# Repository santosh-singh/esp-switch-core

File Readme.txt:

Each device will have its own unique id ... chipid ... ESP.getChipId()
setup()
  When the device is powered on it will check for the ssid password in EEPROM ... and try to connect
  If connected it will resume client mode ... else ... AP mode
    Client mode:
      get deviceid from EEPROM address 100 - 150
      if device does not exist then this device is not registered online
      Check if not device is registered online? /api/1.0/register?deviceid=chipid = returns new deviceid  
      store the deviceid in EEPROM address 100 - 150
      now loop ...
    AP Mode:
      WiFi.mode(WIFI_AP_STA);
      WiFi.softAP( ssid.c_str() );
      Launch Web Server & DNS Server
      display page with SSID list and ask to select one with password.
      attempt to connect as WIFI_STA
      if successful, ESP.restart() else WIFI_display page again ...

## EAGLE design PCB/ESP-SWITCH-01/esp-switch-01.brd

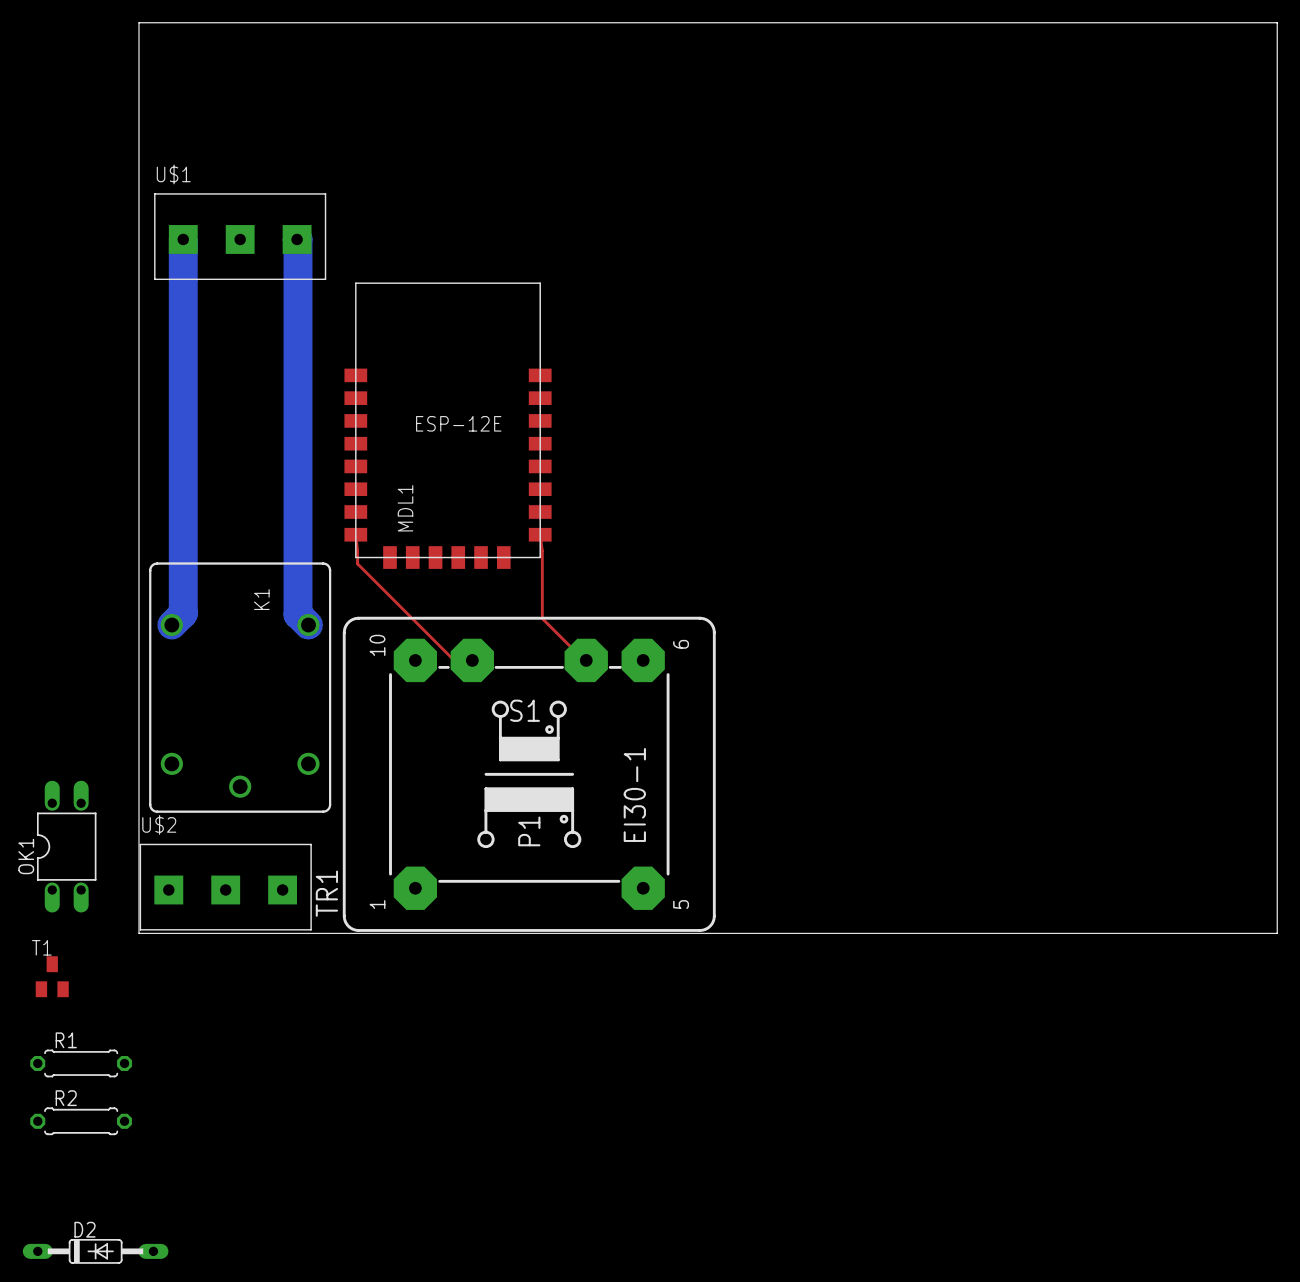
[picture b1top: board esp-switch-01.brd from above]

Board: 2 copper layers, 100.0 x 80.0 mm, 10 parts (0 on the bottom side), 10 nets.

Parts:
D2: 1N4148DO35-10; DO35-10
K1: JS-M1-12V-4; JS-M
MDL1: ESP8266-ESP12E
OK1: PC817; DIL04
R1, R2: 0207/7
T1: BC849; SOT23
TR1: EI30-1
U$1, U$2: TBLOCK_3PIN_5MM; TERMINAL_BLOCK_3_PIN_5_MM

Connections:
GND: MDL1.9, OK1.2, T1.2, TR1.7
LINE1: TR1.1, U$1.P$1, U$2.P$3
LINE2: K1.C, TR1.5, U$2.P$1
unnamed: OK1.3, R1.1
unnamed: K1.NC, U$1.P$2
unnamed: MDL1.5, R2.1
unnamed: K1.NO, U$1.P$3
unnamed: OK1.1, R2.2
unnamed: R1.2, T1.1
VCC: D2.C, K1.1, MDL1.8, TR1.9

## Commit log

2016-08-28 register working
2017-04-26 First Update
2017-08-09 hello
